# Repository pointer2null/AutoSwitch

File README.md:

# AutoSwitch

Auto switch to start a vac or dust collector when a tool starts.

Simple circuit based on the ATTiny85 PCU that monitors the current drawn by a tool, typically a wood working tool such as a saw or planer, and activates a dust collecter when that tool is switched on.

Current is sensed with the ACS712 hall device and the ATTiny85 samples this and after a short delay fires the triac, via an opto isolator, to power on the dust collector.

A seperate relay provides a volt free set of contacts in case blast gates need controlling.

There is a serial port which allows tweaking of the trigger values and time delays.

## Operation

The AtTiny85 uses it's onboard DAC to sample the analogue output from the hall sensor. If this value is above the adcThreshold value, a counter is incremented on each poll, up to the max counter value. If the hall value is below this threshold the counter is decremented. When the counter exceed the on count value and the hall value is above the threadhold, the output triac is switched on. When the count drops below the off count value and the hall value is below the threashold, the triac is switched off. To give a clean shutoff the count value is also set to zero at this point.

## Serial interface

A vac switch doesn't need a seial interface, but I was bored and it got one!

Use the default serial settings: 9600 baud, Data 8, Stop 1, no parity and Xon/Xoff.

A list of commands should be displayed.

- get          : get all config values
- current [n]  : get or set the tool current threshold value
- on [n]       : get or set the on trigger value
- off [n]      : get or set the off trigger value
- count [n]    : get or set the max count value
- period [n]   : get or set the poll period (ms)
- def          : set the default values
- cal          : auto set the current threshold
- watch        : watch the current system values (x to stop)
- fon|foff     : force switch on/off

These allow the internal values to be modified to tweak the behaviour. Values are store in the internal EEPROM.

The **on** value must always be greater than zero and less than the off value.

The **off** value must always be greater that the on value and less than the count max value.

The **count** value must always be greater than the off vlaue.

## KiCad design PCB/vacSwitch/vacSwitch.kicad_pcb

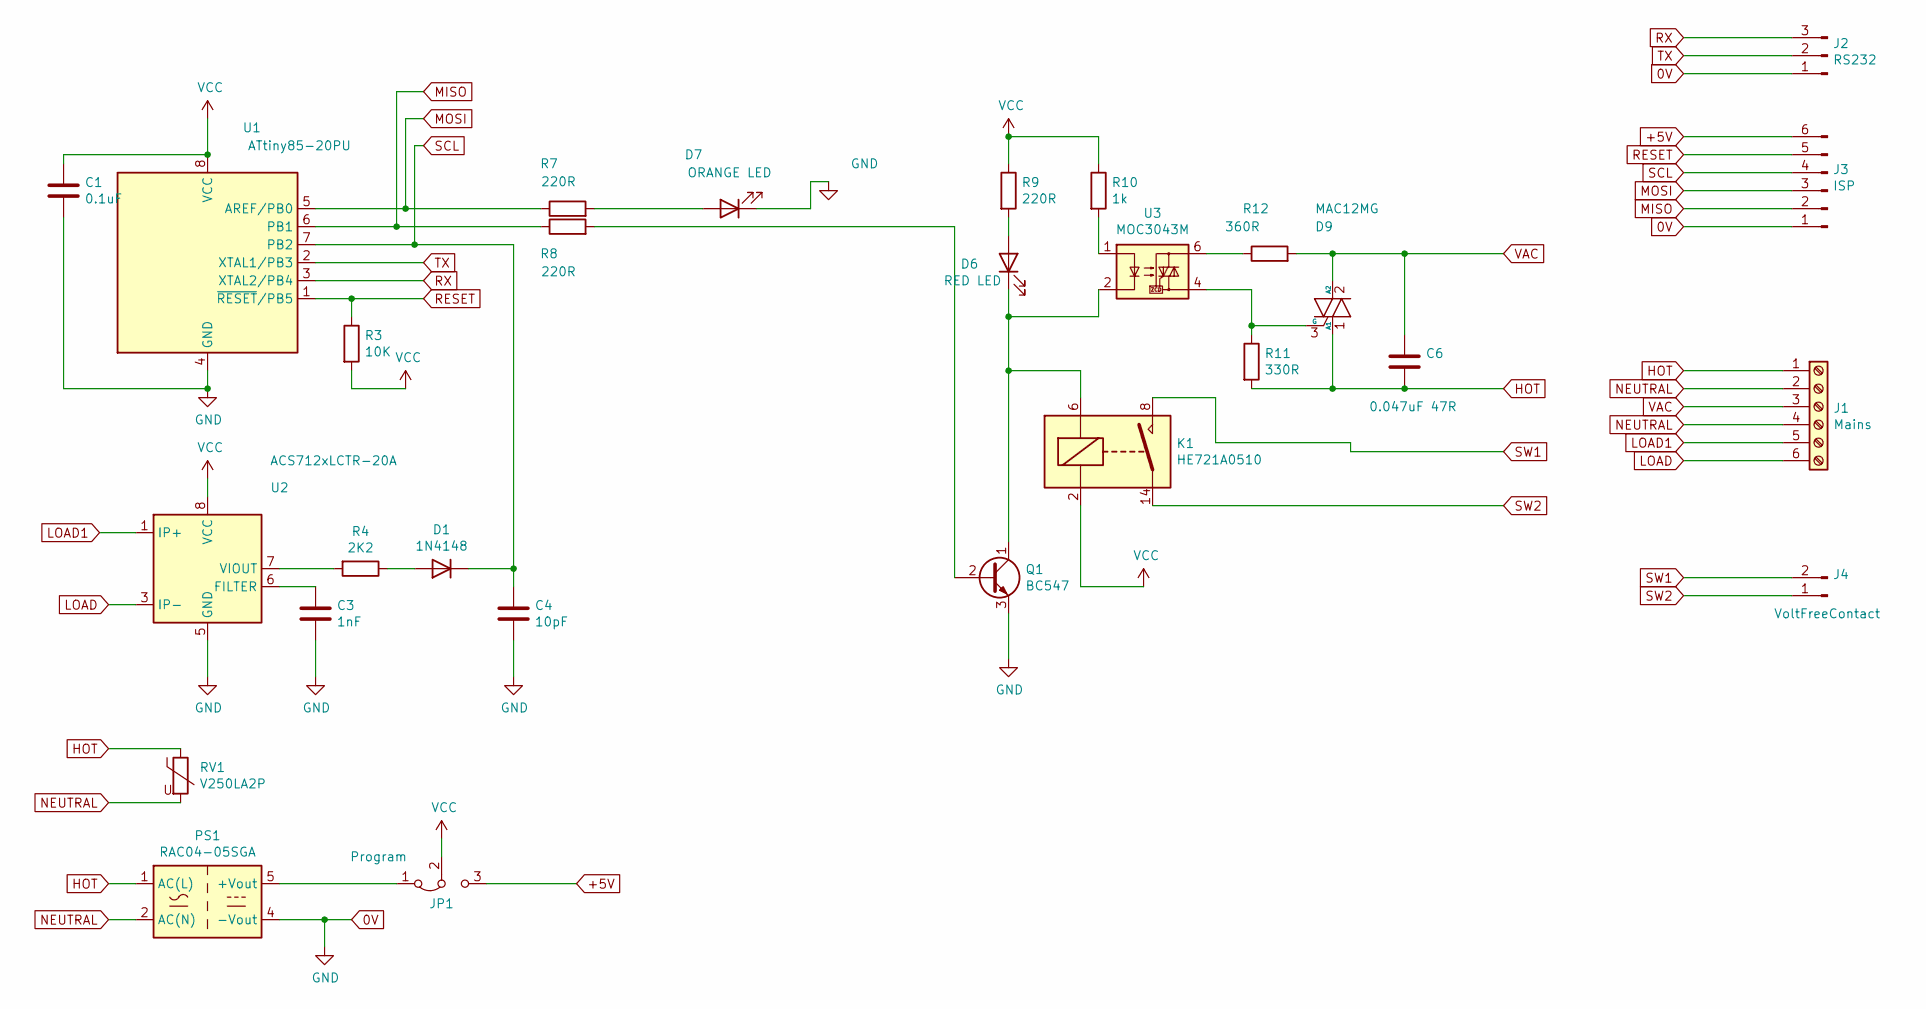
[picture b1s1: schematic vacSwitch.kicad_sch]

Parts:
C1: 0.1uF; CP_Radial_Tantal_D5.0mm_P5.00mm
C3: 1nF; CP_Radial_Tantal_D6.0mm_P5.00mm
C4: 10pF; CP_Radial_Tantal_D5.0mm_P5.00mm
C6: 0.047uF 47R; C_Rect_L16.5mm_W7.0mm_P15.00mm_MKT
D1: 1N4148; D_DO-35_SOD27_P7.62mm_Horizontal
D6: RED LED; LED_D3.0mm
D7: ORANGE LED; LED_D3.0mm
D9: MAC12MG; TO-220-3_Vertical
J1: Mains; 1729160
J2: RS232; JST_PH_B3B-PH-K_1x03_P2.00mm_Vertical
J3: ISP; JST_PH_B6B-PH-K_1x06_P2.00mm_Vertical
J4: VoltFreeContact; JST_PH_B2B-PH-K_1x02_P2.00mm_Vertical
JP1: Program; PinHeader_1x03_P2.54mm_Vertical
K1: HE721A0510; Relay_StandexMeder_DIP_LowProfile
PS1: RAC04-05SGA; Converter_ACDC_RECOM_RAC04-xxSGx_THT
Q1: BC547; TO-92_Inline
R3: 10K; R_Axial_DIN0207_L6.3mm_D2.5mm_P7.62mm_Horizontal
R4: 2K2; R_Axial_DIN0207_L6.3mm_D2.5mm_P7.62mm_Horizontal
R7, R8, R9: 220R; R_Axial_DIN0207_L6.3mm_D2.5mm_P7.62mm_Horizontal
R10: 1k; R_Axial_DIN0207_L6.3mm_D2.5mm_P7.62mm_Horizontal
R11: 330R; R_Axial_DIN0207_L6.3mm_D2.5mm_P7.62mm_Horizontal
R12: 360R; R_Axial_DIN0207_L6.3mm_D2.5mm_P7.62mm_Horizontal
RV1: V250LA2P; RV_Disc_D7mm_W3.9mm_P5mm
U1: ATtiny85-20PU; DIP-8_W7.62mm_LongPads
U2: ACS712xLCTR-20A; SOIC-8_3.9x4.9mm_P1.27mm
U3: MOC3043M; DIP-6_W7.62mm_LongPads

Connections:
0V: C1.2, C3.2, C4.2, D7.1 (K), J2.1, J3.1, PS1.4 (-Vout), Q1.3 (E), U1.4 (GND), U2.5 (GND)
+5V: J3.6, JP1.3 (B)
HOT: C6.2, D9.1 (A1), J1.1, PS1.1 (AC(L)), R11.2, RV1.1
LOAD: J1.6, U2.3 (IP-), U2.4 (IP-)
LOAD1: J1.5, U2.1 (IP+), U2.2 (IP+)
MISO: J3.2, R8.1, U1.6 (PB1)
MOSI: J3.3, R7.1, U1.5 (AREF/PB0)
NEUTRAL: J1.2, J1.4, PS1.2 (AC(N)), RV1.2
unnamed: C3.1, U2.6 (FILTER)
unnamed: D1.2 (A), R4.1
unnamed: D6.1 (K), K1.6, Q1.1 (C), U3.2
unnamed: D6.2 (A), R9.2
unnamed: D7.2 (A), R7.2
unnamed: D9.3 (G), R11.1, U3.4
unnamed: JP1.1 (A), PS1.5 (+Vout)
unnamed: Q1.2 (B), R8.2
unnamed: R4.2, U2.7 (VIOUT)
unnamed: R10.2, U3.1
unnamed: R12.1, U3.6
RESET: J3.5, R3.1, U1.1 (~RESET/PB5)
RX: J2.3, U1.3 (XTAL2/PB4)
SCL: C4.1, D1.1 (K), J3.4, U1.7 (PB2)
SW1: J4.2, K1.8
SW2: J4.1, K1.14
TX: J2.2, U1.2 (XTAL1/PB3)
VAC: C6.1, D9.2 (A2), J1.3, R12.2
VCC: C1.1, JP1.2 (C), K1.2, R3.2, R9.1, R10.1, U1.8 (VCC), U2.8 (VCC)

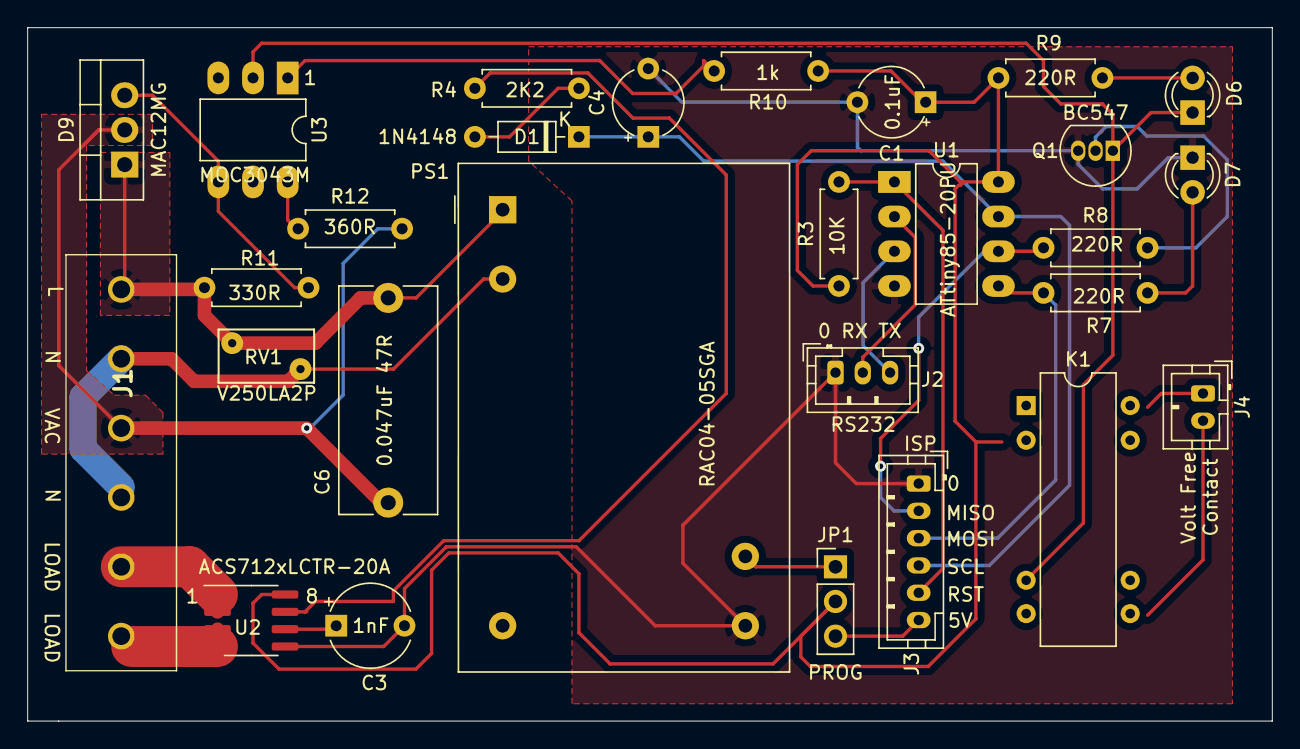
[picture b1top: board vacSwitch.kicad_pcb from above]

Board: 2 copper layers, 91.2 x 50.8 mm, 28 parts (0 on the bottom side), 27 nets.

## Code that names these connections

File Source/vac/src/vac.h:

#include <Arduino.h>
#include "SerialCommands.h"

void valuesHeader();
void valuesDump();
void useage();
void cmd_get(SerialCommands* sender);
void cmd_current(SerialCommands* sender);
void cmd_period(SerialCommands* sender);
void cmd_count(SerialCommands* sender);
void cmd_watch(SerialCommands* sender);
void cmd_stop_watch(SerialCommands* sender);
void cmd_cal(SerialCommands* sender);
void cmd_setOn(SerialCommands* sender);
void cmd_setOff(SerialCommands* sender);
void cmd_setDef(SerialCommands* sender);
void cmd_setFOff(SerialCommands* sender);
void cmd_setFOn(SerialCommands* sender);
void setDefaults();
void periodicCheck();

#define blinkPin 0                     // pin 5, PB0
#define relay    1                     // pin 6, PB1
#define serialTX 3                     // pin 2, PB3
#define serialRX 4                     // pin 3, PB4
#define sense    A1                    // pin 7, PB2, ADC1

// 0.00488V (4.88mV) per unit on the ADC
// 2.5V (zero current = 512) (defaul using Vcc as ref)
// ACS712-20A has a sensitivity of 100mV/A
// So 1A = 100mV
// Means we should see a adc increase of around 20 per amp.
// 1A @ 240V is 240W  
#define defaultCurrentThreshold  520   // ADC trigger level : approx 17 counts => 200W
#define defaultThresholdCountMax 10    // max counter value - affects how long we stay on after the tool is off
#define defaultThresholdOn       3     // count point to switch on
#define defaultThresholdOff      6     // count point to switch off
#define defaultCheckPeriodMs     500   // loop poll frequency

#define calPeriodMs              10000 // 10 seconds

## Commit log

2021-10-23 Initial files
2021-10-23 added the serial library and handler.
    remembered how shit c is for programming.
2021-10-24 Totally OTT serial control!
2021-10-24 Minimal version
2021-10-24 Added the serial command library as modified
2021-11-26 serial
2021-11-30 Move and added PCB
2021-11-30 erronious file
2021-11-30 arduino needs the vac folder
2021-11-30 non blocking blink
2021-11-30 serial command - adjust hold value
2021-12-07 fixed the flashing led issue and a few more problems
    Serial values editor needs a tweak and so do the defaul values. On
    and off loginc may want a look as we stay on too long
2021-12-07 serial updates and trigger updates
2021-12-07 add set to default
2021-12-14 added force switch on and off
2021-12-14 update PCB (errors fixed)
2021-12-14 missing files
2021-12-15 Board updates. V1.1
2021-12-28 More serial and board tweaks
2021-12-28 extended readme
2021-12-28 added vscode readme
2021-12-28 removed second older readme
2021-12-28 test
2021-12-29 Updated defaults. Fixed count serial command.
    Tested and works with 200W tool load and 2kW dust collector load.
2022-01-03 Converted to cpp, moved to platformIO
2022-01-03 removing old files
2022-06-18 Defaults tweak
